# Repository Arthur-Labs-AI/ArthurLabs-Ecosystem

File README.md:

# ArthurLabs Ecosystem

Monorepo for the ArthurLabs products: **Nexus**, an AI engineering harness; **Sentry**, a local-first AI QA desktop app; **A.R.T.H.U.R.**, a local-first knowledge app; and the **ArthurLabs website**.

| Project | Path | What it is | Stack |
| --- | --- | --- | --- |
| **Nexus** | [`systems/nexus`](systems/nexus) | AI engineering assistant. A deterministic controller owns routing, attempts, verification and completion; the model implements. Ships in two editions: **Nexus DSH** and **Nexus Native** (see below). | Rust, Tauri v2, React, TypeScript, PowerShell/POSIX installers |
| **Sentry** | [`systems/sentry`](systems/sentry) | Local-first AI QA. OpenCode, DeepSeek and GLM (via Claude Code) independently investigate one immutable project snapshot and return findings, evidence, token usage and persistent run history. | TypeScript, pnpm + Turbo monorepo, Electron desktop, CLI |
| **A.R.T.H.U.R.** | [`systems/arthur`](systems/arthur) | Local-first knowledge app. Captures text and Android voice, distills it into knowledge objects with source provenance, projects, relations and immutable revision history, with recall and review-first evolution. One native runtime owns an app-local SQLite store. | Tauri v2, React, TypeScript, Rust, Android |
| **Website** | [`website`](website) | Marketing site for the ArthurLabs product line (Suite, Studio, Nexus, Sentry, Hardware). | Next.js, React, Tailwind, GSAP, Playwright |

Studio and Hardware appear as pages on the website only. Their implementations are not in this repository. Import history: [Nexus](docs/integration/NEXUS-IMPORT-REPORT.md), [Sentry](docs/integration/SENTRY-IMPORT-REPORT.md), [A.R.T.H.U.R.](docs/integration/ARTHUR-IMPORT-REPORT.md).

## Repository layout

```
.
├── systems/
│   ├── nexus/
│   │   ├── native/             Nexus Native: Rust workspace (kernel, broker, daemon, CLI, tools, store, runtime)
│   │   ├── apps/nexus-desktop  Nexus Native desktop app (Tauri, React + Rust) and release packaging
│   │   ├── runtime/, ui/       Nexus DSH: pinned DSH runtime, vendored agent, patches, Control Room UI
│   │   ├── bin/, config/, scripts/  `aih` commands, profiles, registry config, helpers (DSH)
│   │   ├── docs/               Architecture, operations, Linux guide
│   │   └── setup.sh, setup.ps1 Installers (Linux, Windows) for Nexus DSH
│   ├── sentry/
│   │   ├── apps/               desktop, cli, runtime
│   │   ├── packages/           run-engine, snapshot-engine, harnesses (claude-code, deepseek, opencode), persistence, ...
│   │   └── docs/               Setup, security, architecture, ADRs
│   └── arthur/
│       ├── apps/arthur         Tauri app (React UI + Rust runtime + SQLite store), Android
│       ├── packages/, src/     Shared packages and the older CLI/HTTP TypeScript runtime (frozen)
│       └── docs/, hardware/    Architecture, milestone gates, hardware notes
├── website/                    Next.js site (self-contained)
├── docs/integration/           Import and validation reports
└── .github/workflows/          CI: Nexus release workflow
```

## Nexus

Nexus moves engineering state out of the model and into deterministic controller records. Task identity, attempts, verification evidence, review requirements and completion live in the controller, and the UI observes that state. Key points:

- Execution classes (`deterministic`, `engineer_normal`, `engineer_deep`, `reviewer`, `solver`) bound to models by an engineering profile.
- Independent, read-only review when policy requires it.
- Durable task state and fail-closed behavior on missing or corrupt records.

Details: [`systems/nexus/README.md`](systems/nexus/README.md) and [`systems/nexus/docs`](systems/nexus/docs).

### Two editions

Both editions are maintained. Neither replaces the other.

| | **Nexus DSH** | **Nexus Native** |
| --- | --- | --- |
| Built on | The DeepSeek Harness (DSH) runtime: its sessions, tools, permissions, Git integration and web UI | A Rust engine with its own kernel, broker, daemon and sandboxed tools |
| Interface | Universal Nexus app and Control Room, opened with `aih -Open` | Tauri desktop app |
| Install | `setup.sh` (Linux) or `setup.ps1` (Windows) | `.deb` / `.dmg` from [Releases](https://github.com/Arthur-Labs-AI/ArthurLabs-Ecosystem/releases), or build from source |
| Platforms | Windows and Linux x86_64 | Linux x86_64 and macOS Apple Silicon |
| Code | `runtime/`, `ui/`, `bin/`, `config/`, `scripts/` | `native/`, `apps/nexus-desktop/` |

### Platform support

| Platform | Nexus DSH | Nexus Native |
| --- | --- | --- |
| Linux x86_64 | Supported | Full app: engine, sandbox, `.deb` package (Debian/Ubuntu, glibc 2.39+) |
| Linux ARM64 | Not documented | Development builds (Fedora 44 verified). Release packaging does not target ARM64. |
| macOS (Apple Silicon) | Not documented | Full app. The sandboxed Linux engine runs in an embedded headless microVM (Apple Virtualization.framework, no UTM or SSH), about 3 s to ready. Builds without the engine image are a UI-only shell. See [`M4-EMBEDDED-ENGINE-REPORT.md`](systems/nexus/M4-EMBEDDED-ENGINE-REPORT.md). |
| Windows | Supported | Not part of the native release workflow |

### Run Nexus DSH from source

Linux (user-scoped install, no sudo):

```sh
cd systems/nexus
./setup.sh
aih-key        # set your provider key
aih -Open      # open the app
```

Windows: run `setup.ps1` from PowerShell. See [`systems/nexus/README.md`](systems/nexus/README.md) and the [Linux guide](systems/nexus/docs/linux.md).

### Run Nexus Native from source

Needs Rust and Node.js 22+. On Fedora, first install `gtk3-devel webkit2gtk4.1-devel librsvg2-devel patchelf`.

```sh
cd systems/nexus/apps/nexus-desktop
npm ci
npm run desktop
```

See [`apps/nexus-desktop/README.md`](systems/nexus/apps/nexus-desktop/README.md) for environment variables and troubleshooting.

### Checks

```sh
# Nexus Native frontend
cd systems/nexus/apps/nexus-desktop
npm run typecheck && npm run lint && npm test

# Nexus Native Rust workspace
cd systems/nexus/native
cargo fmt --check && cargo clippy --all-targets && cargo test

# Nexus DSH
cd systems/nexus
aih-test
```

## Sentry

Sentry imports a project into a managed copy with an immutable revision, then lets one to three agents investigate it independently. Projects and history stay local. Selected agents send relevant source and evidence to the providers you configure, so review their policies before importing confidential code.

- **Platform:** Windows 11 x64 with WSL2 (Ubuntu preferred). Native Linux desktop is deferred.
- **Latest stable:** [Sentry v1.0.2](https://github.com/Mert1026/Sentry/releases/tag/v1.0.2). The ZIP is unsigned and bootstraps its Linux runtime online. There is no automatic updater.
- **Install and use:** `sentry setup`, `sentry open`, `sentry doctor`, and `sentry cli ... --json` for automation. See [`systems/sentry/README.md`](systems/sentry/README.md).

Develop (Node 22+, pnpm 9.12.3):

```sh
cd systems/sentry
pnpm install --frozen-lockfile
pnpm build
pnpm test
pnpm --filter @qa/desktop dev:electron
```

Development needs a Linux or WSL environment with systemd user services, bubblewrap and socat. See [`CONTRIBUTING.md`](systems/sentry/CONTRIBUTING.md) and the [documentation index](systems/sentry/docs/README.md).

## A.R.T.H.U.R.

A.R.T.H.U.R. keeps your knowledge in an app-local SQLite store owned by one native runtime; the UI reaches it through `ArthurClient` and native commands. Model responses only *propose* candidates. Native code validates authority, source spans and expected revisions before anything is committed. Cloud features need provider credentials and can send relevant content to the selected provider.

- **Status:** in development. M05 synchronization is a dormant qualification candidate, not an enabled feature. Production stays on schema v9 with closed trust/LAN activation. See [M05 readiness](systems/arthur/docs/architecture/m05-activation-readiness.md).
- **Legacy runtime:** the older CLI/HTTP TypeScript runtime under `src/` is under a [frozen subsystem policy](systems/arthur/docs/competition/FROZEN_SUBSYSTEMS.md) and is not the app's authoritative store.

Develop (Node.js 24.13.1 and Rust 1.99.1 in CI):

```sh
cd systems/arthur
npm ci
npm run arthur:install
npm run arthur:dev                # browser preview with a native-free client (no SQLite)
cd apps/arthur && npm run tauri -- dev   # the real native app
```

Android builds need the JDK, Android SDK/NDK and the Rust Android target. See [`systems/arthur/README.md`](systems/arthur/README.md) and [`apps/arthur/README.md`](systems/arthur/apps/arthur/README.md).

Checks (from `systems/arthur`): `npm run test:architecture` and `npm run arthur:check`, plus `cargo fmt`, `cargo clippy` and `cargo test` against `apps/arthur/src-tauri/Cargo.toml` as listed in its README.

## Website

```sh
cd website
npm ci
npm run dev        # http://localhost:3000
npm run build
npm run typecheck
```

Needs Node.js 20.9+. End-to-end tests run with Playwright against the production export. See [`website/README.md`](website/README.md) for the full procedure, routes and structure.

## Releases

**Nexus Native** installers are built by [`.github/workflows/nexus-release.yml`](.github/workflows/nexus-release.yml):

- Trigger: push a `nexus-v*` tag, or run **Nexus release** from the Actions tab with a tag name.
- Linux job: builds and content-verifies the `.deb`.
- Engine image job: builds the Fedora ARM64 guest image and kernel on an ARM64 Linux runner.
- macOS job: builds the app with the embedded VM engine and packages the arm64 `.dmg` (about 430 MB). It is ad-hoc signed and not notarized, so Gatekeeper will warn on first launch (right-click, then Open).
- The workflow creates a **draft** GitHub release with both installers and SHA-256 files. It never publishes on its own.

Published builds are listed under [Releases](https://github.com/Arthur-Labs-AI/ArthurLabs-Ecosystem/releases). Sentry releases are published separately on its own repository (link above).

## Contributing

- Commits follow Conventional Commits with a scope: `feat(native): …`, `fix(registry): …`, `docs: …`, `test(native): …`.
- Branches are named `type/short-slug`, for example `feat/nexus-release-workflow`.
- Work in the subproject you are changing and run its checks before opening a PR.
- A.R.T.H.U.R. enforces architecture boundaries in CI (`npm run test:architecture`); run it before opening a PR.
- Sentry has its own rules (branching, review, agent instruction files): read [`systems/sentry/CONTRIBUTING.md`](systems/sentry/CONTRIBUTING.md) first.

## Security

Never commit provider keys, `auth.json`, `.env` files, logs, or session captures. If a credential is committed, rotate it right away. See [`systems/nexus/SECURITY.md`](systems/nexus/SECURITY.md) and the Sentry [threat model](systems/sentry/docs/security/V1_THREAT_MODEL.md).

## License

Licenses are per project:

- **Sentry:** MIT, see [`systems/sentry/LICENSE`](systems/sentry/LICENSE).
- **A.R.T.H.U.R.:** `UNLICENSED` in its `package.json` (proprietary, no open-source license).
- **Nexus and website:** no license file yet. Until one is added, all rights are reserved by the authors.

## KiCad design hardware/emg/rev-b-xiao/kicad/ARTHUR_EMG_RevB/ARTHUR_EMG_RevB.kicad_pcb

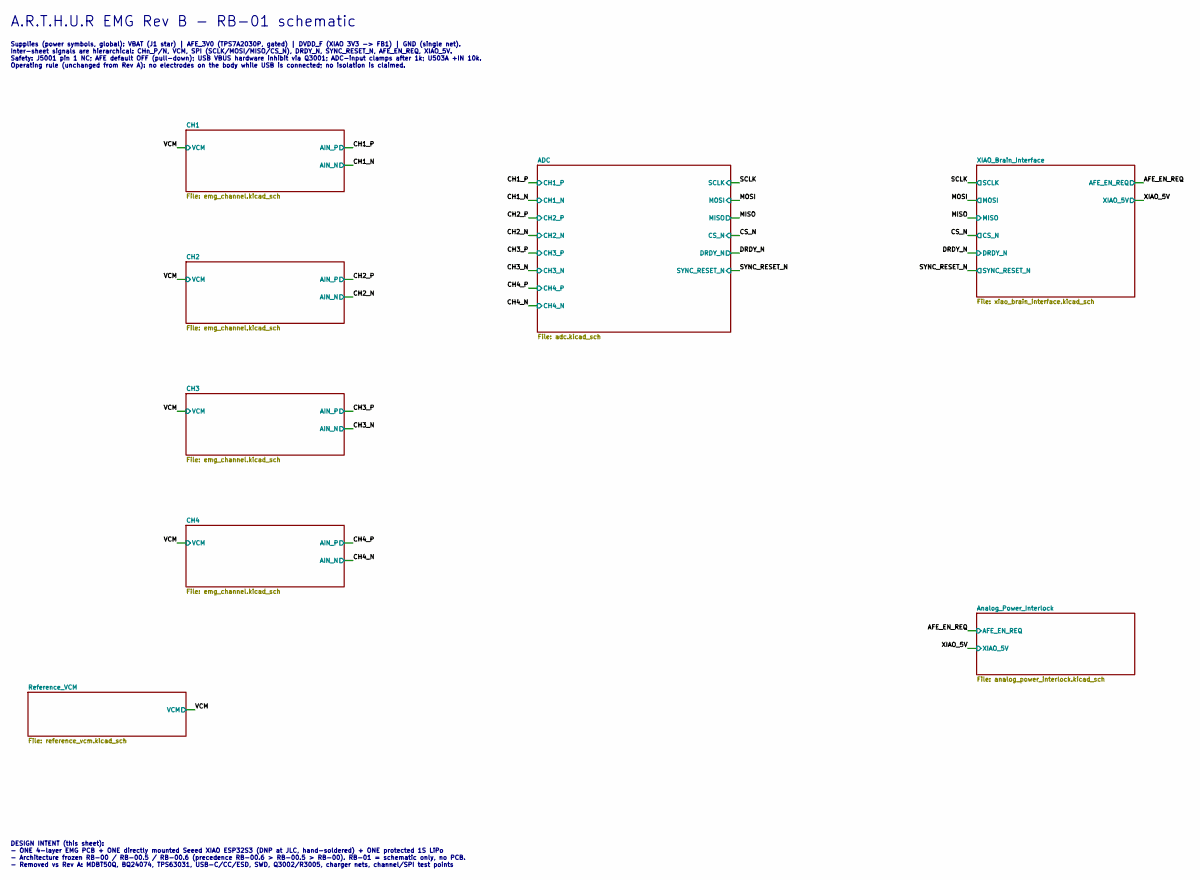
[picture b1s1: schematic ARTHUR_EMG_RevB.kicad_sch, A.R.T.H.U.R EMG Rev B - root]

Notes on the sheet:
DESIGN INTENT (this sheet): - ONE 4-layer EMG PCB + ONE directly mounted Seeed XIAO ESP32S3 (DNP at JLC, hand-soldered) + ONE protected 1S LiPo - Architecture frozen RB-00 / RB-00.5 / RB-00.6 (precedence RB-00.6 > RB-00.5 > RB-00). RB-01 = schematic only, no PCB. - Removed vs Rev A: MDBT50Q, BQ2407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
A.R.T.H.U.R EMG Rev B - RB-01 schematic
Supplies (power symbols, global): VBAT (J1 star) | AFE_3V0 (TPS7A2030P, gated) | DVDD_F (XIAO 3V3 -> FB1) | GND (single net). Inter-sheet signals are hierarchical: CHn_P/N, VCM, SPI (SCLK/MOSI/MISO/CS_N), DRDY_N, SYNC_RESET_N, AFE_EN_REQ, XIAO_5V. Safety: J5001 pin 1 NC; AFE default OFF (pull-down)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

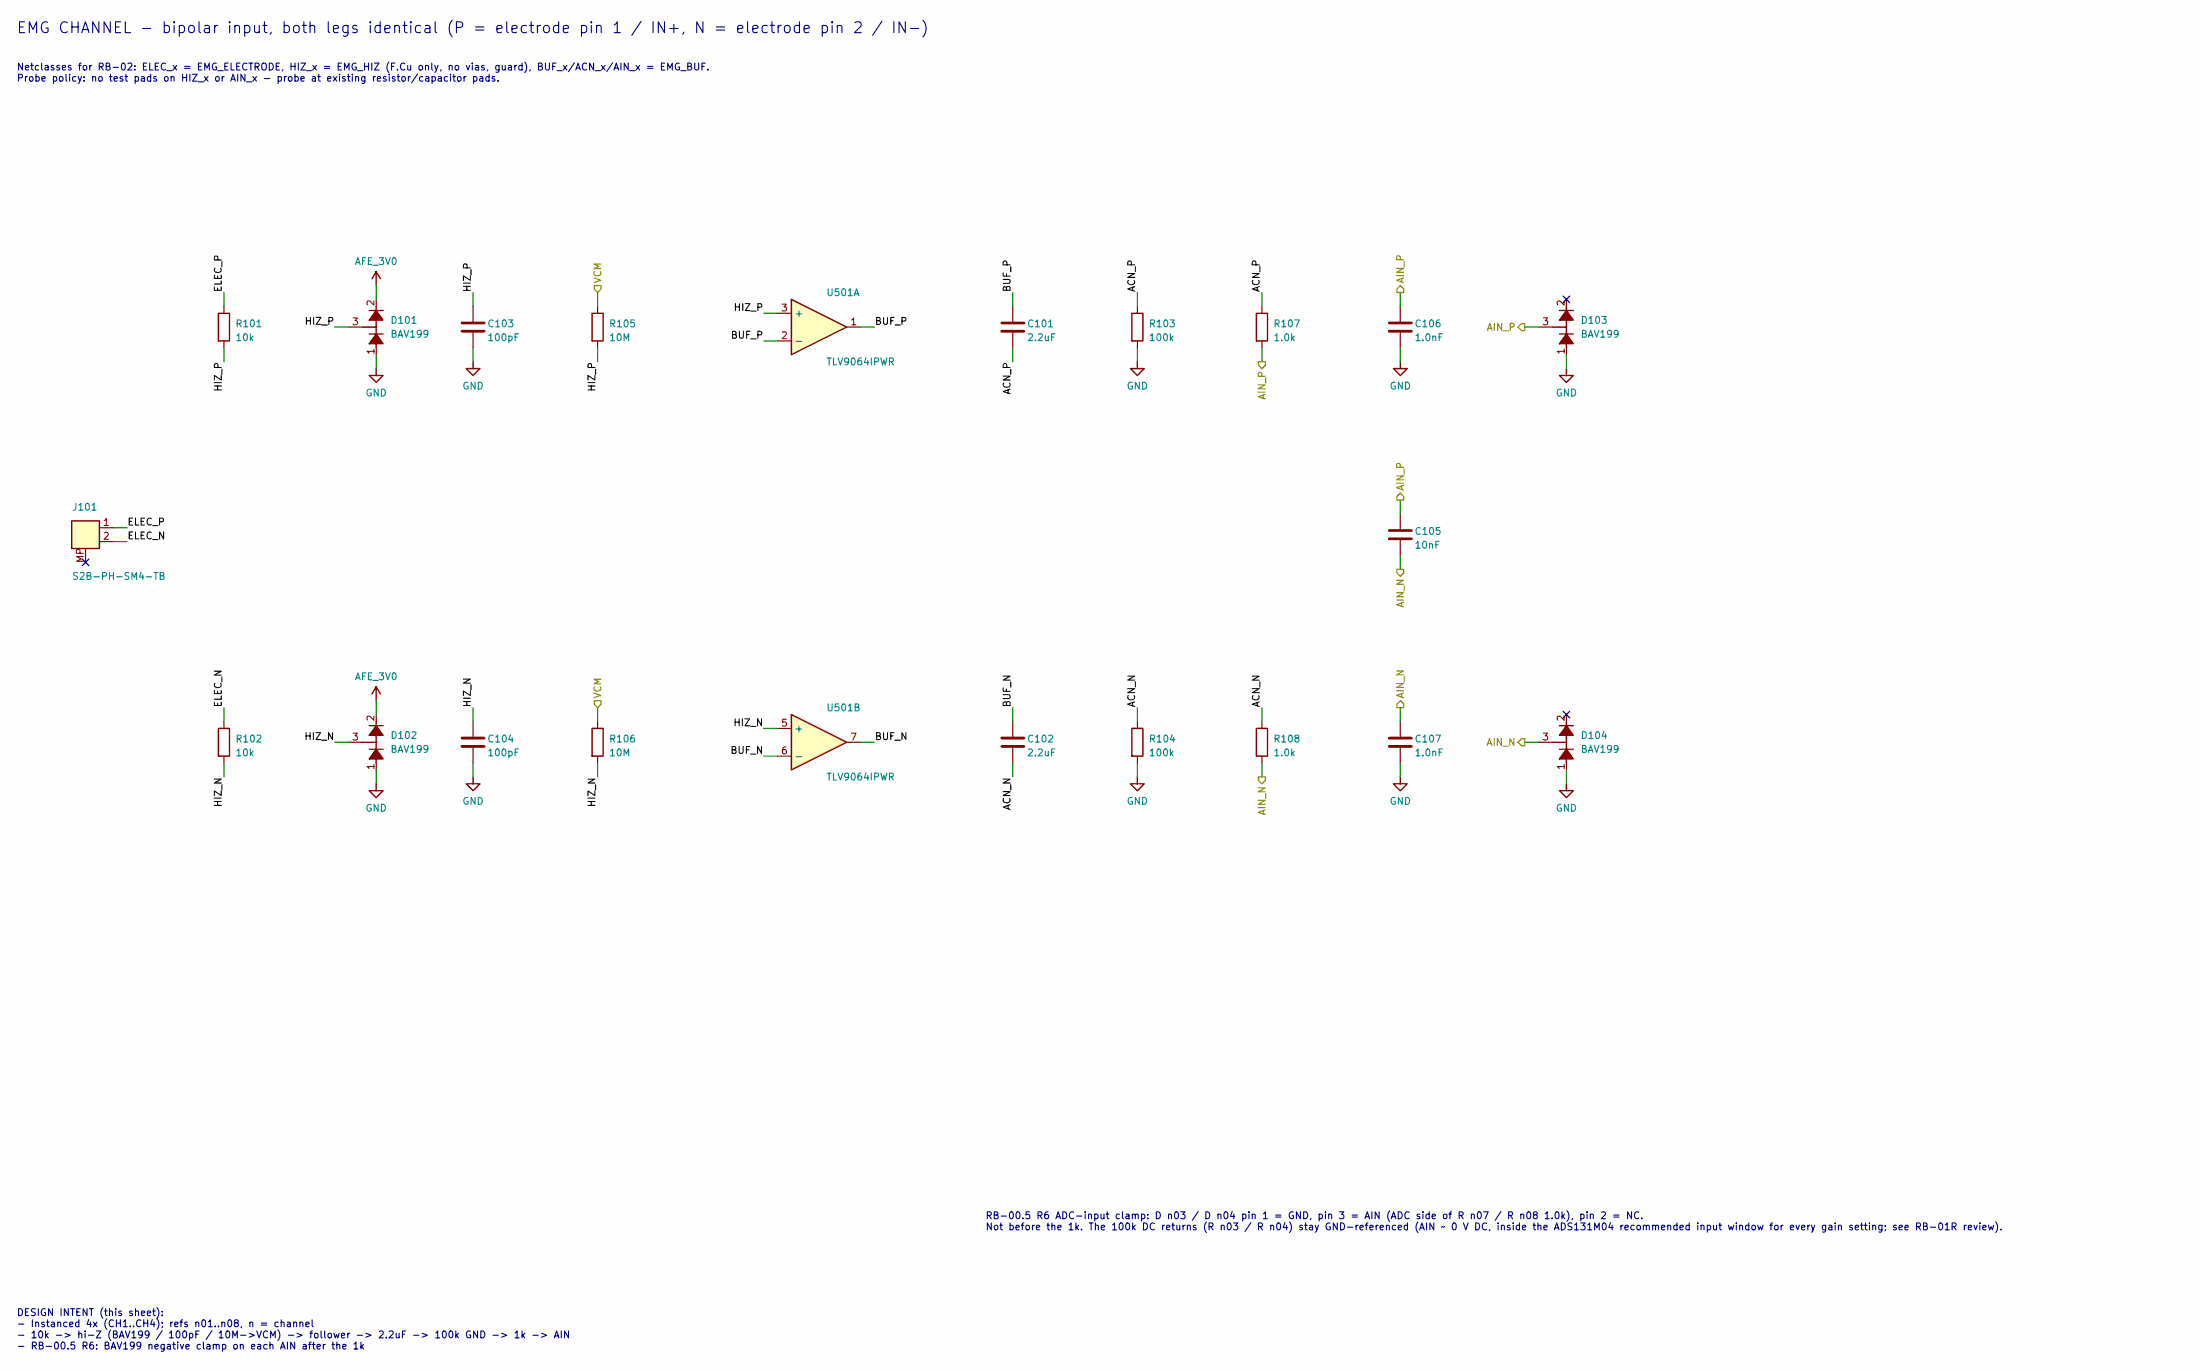
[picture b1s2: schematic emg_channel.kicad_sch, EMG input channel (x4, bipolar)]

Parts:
C101, C102: 2.2uF; C_0603_1608Metric; MPN 0603B225K160NT; LCSC C43922
C103, C104: 100pF; C_0603_1608Metric; MPN CL10C101JB8NNNC; LCSC C14858
C105: 10nF; C_0603_1608Metric; MPN C1608C0G1H103JT000N; LCSC C76599
C106, C107: 1.0nF; C_0603_1608Metric; MPN 0603CG102J500NT; LCSC C1636
D101, D102, D103, D104: BAV199; SOT-23; MPN BAV199,215; LCSC C40919
J101: S2B-PH-SM4-TB; JST_PH_S2B-PH-SM4-TB_1x02-1MP_P2.00mm_Horizontal; MPN S2B-PH-SM4-TB(LF)(SN); LCSC C295747
R101, R102: 10k; R_0603_1608Metric; MPN RC0603FR-0710KL; LCSC C98220
R103, R104: 100k; R_0603_1608Metric; MPN 0603WAF1003T5E; LCSC C25803
R105, R106: 10M; R_0603_1608Metric; MPN RC0603FR-0710ML; LCSC C114606
R107, R108: 1.0k; R_0603_1608Metric; MPN 0603WAF1001T5E; LCSC C21190
U501: TLV9064IPWR; TSSOP-14_4.4x5mm_P0.65mm; MPN TLV9064IPWR; LCSC C779410

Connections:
/CH1/ACN_N: C102.2, R104.1, R108.1
/CH1/ACN_P: C101.2, R103.1, R107.1
/CH1/BUF_N: C102.1, U501.6 (-), U501.7
/CH1/BUF_P: C101.1, U501.1, U501.2 (-)
/CH1/ELEC_N: J101.2, R102.1
/CH1/ELEC_P: J101.1, R101.1
/CH1/HIZ_N: C104.1, D102.3 (K1/A2), R102.2, R106.2, U501.5 (+)
/CH1/HIZ_P: C103.1, D101.3 (K1/A2), R101.2, R105.2, U501.3 (+)
/CH1_N: C105.2, C107.1, D104.3 (K1/A2), R108.2; also elsewhere on the board
/CH1_P: C105.1, C106.1, D103.3 (K1/A2), R107.2; also elsewhere on the board
/CH2/BUF_N: U501.13 (-), U501.14; also elsewhere on the board
/CH2/BUF_P: U501.8, U501.9 (-); also elsewhere on the board
/CH2/HIZ_N: U501.12 (+); also elsewhere on the board
/CH2/HIZ_P: U501.10 (+); also elsewhere on the board
/VCM: R105.1, R106.1; also elsewhere on the board
AFE_3V0: D101.2 (K2), D102.2 (K2); also elsewhere on the board
GND: C103.2, C104.2, C106.2, C107.2, D101.1 (A1), D102.1 (A1), D103.1 (A1), D104.1 (A1), R103.2, R104.2; also elsewhere on the board

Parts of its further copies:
C201, C202, C301, C302, C401, C402: 2.2uF; C_0603_1608Metric; MPN 0603B225K160NT; LCSC C43922
C203, C204, C303, C304, C403, C404: 100pF; C_0603_1608Metric; MPN CL10C101JB8NNNC; LCSC C14858
C205, C305, C405: 10nF; C_0603_1608Metric; MPN C1608C0G1H103JT000N; LCSC C76599
C206, C207, C306, C307, C406, C407: 1.0nF; C_0603_1608Metric; MPN 0603CG102J500NT; LCSC C1636
D201, D202, D203, D204, D301, D302, D303, D304, D401, D402, D403, D404: BAV199; SOT-23; MPN BAV199,215; LCSC C40919
J201, J301, J401: S2B-PH-SM4-TB; JST_PH_S2B-PH-SM4-TB_1x02-1MP_P2.00mm_Horizontal; MPN S2B-PH-SM4-TB(LF)(SN); LCSC C295747
R201, R202, R301, R302, R401, R402: 10k; R_0603_1608Metric; MPN RC0603FR-0710KL; LCSC C98220
R203, R204, R303, R304, R403, R404: 100k; R_0603_1608Metric; MPN 0603WAF1003T5E; LCSC C25803
R205, R206, R305, R306, R405, R406: 10M; R_0603_1608Metric; MPN RC0603FR-0710ML; LCSC C114606
R207, R208, R307, R308, R407, R408: 1.0k; R_0603_1608Metric; MPN 0603WAF1001T5E; LCSC C21190

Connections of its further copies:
/CH2/ACN_N: C202.2, R204.1, R208.1
/CH2/ACN_P: C201.2, R203.1, R207.1
/CH2/BUF_N: C202.1; also elsewhere on the board
/CH2/BUF_P: C201.1; also elsewhere on the board
/CH2/ELEC_N: J201.2, R202.1
/CH2/ELEC_P: J201.1, R201.1
/CH2/HIZ_N: C204.1, D202.3 (K1/A2), R202.2, R206.2; also elsewhere on the board
/CH2/HIZ_P: C203.1, D201.3 (K1/A2), R201.2, R205.2; also elsewhere on the board
/CH2_N: C205.2, C207.1, D204.3 (K1/A2), R208.2; also elsewhere on the board
/CH2_P: C205.1, C206.1, D203.3 (K1/A2), R207.2; also elsewhere on the board
/CH3/ACN_N: C302.2, R304.1, R308.1
/CH3/ACN_P: C301.2, R303.1, R307.1
/CH3/BUF_N: C302.1; also elsewhere on the board
/CH3/BUF_P: C301.1; also elsewhere on the board
/CH3/ELEC_N: J301.2, R302.1
/CH3/ELEC_P: J301.1, R301.1
/CH3/HIZ_N: C304.1, D302.3 (K1/A2), R302.2, R306.2; also elsewhere on the board
/CH3/HIZ_P: C303.1, D301.3 (K1/A2), R301.2, R305.2; also elsewhere on the board
/CH3_N: C305.2, C307.1, D304.3 (K1/A2), R308.2; also elsewhere on the board
/CH3_P: C305.1, C306.1, D303.3 (K1/A2), R307.2; also elsewhere on the board
/CH4/ACN_N: C402.2, R404.1, R408.1
/CH4/ACN_P: C401.2, R403.1, R407.1
/CH4/BUF_N: C402.1; also elsewhere on the board
/CH4/BUF_P: C401.1; also elsewhere on the board
/CH4/ELEC_N: J401.2, R402.1
/CH4/ELEC_P: J401.1, R401.1
/CH4/HIZ_N: C404.1, D402.3 (K1/A2), R402.2, R406.2; also elsewhere on the board
/CH4/HIZ_P: C403.1, D401.3 (K1/A2), R401.2, R405.2; also elsewhere on the board
/CH4_N: C405.2, C407.1, D404.3 (K1/A2), R408.2; also elsewhere on the board
/CH4_P: C405.1, C406.1, D403.3 (K1/A2), R407.2; also elsewhere on the board
/VCM: R205.1, R206.1, R305.1, R306.1, R405.1, R406.1; also elsewhere on the board
AFE_3V0: D201.2 (K2), D202.2 (K2), D301.2 (K2), D302.2 (K2), D401.2 (K2), D402.2 (K2); also elsewhere on the board
GND: C203.2, C204.2, C206.2, C207.2, C303.2, C304.2, C306.2, C307.2, C403.2, C404.2, C406.2, C407.2, D201.1 (A1), D202.1 (A1), D203.1 (A1), D204.1 (A1), D301.1 (A1), D302.1 (A1), D303.1 (A1), D304.1 (A1), D401.1 (A1), D402.1 (A1), D403.1 (A1), D404.1 (A1), R203.2, R204.2, R303.2, R304.2, R403.2, R404.2; also elsewhere on the board

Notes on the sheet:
EMG CHANNEL - bipolar input, both legs identical (P = electrode pin 1 / IN+, N = electrode pin 2 / IN-)
Netclasses for RB-02: ELEC_x = EMG_ELECTRODE, HIZ_x = EMG_HIZ (F.Cu only, no vias, guard), BUF_x/ACN_x/AIN_x = EMG_BUF. Probe policy: no test pads on HIZ_x or AIN_x - probe at existing resistor/capacitor pads.
RB-00.5 R6 ADC-input clamp: D n03 / D n04 pin 1 = GND, pin 3 = AIN (ADC side of R n07 / R n08 1.0k), pin 2 = NC. Not before the 1k. The 100k DC returns (R n03 / R n04) stay GND-referenced (AIN ~ 0 V DC, inside the ADS131M04 recommended input window for every gain setting; see RB-01R review).
DESIGN INTENT (this sheet): - Instanced 4x (CH1..CH4); refs n01..n08, n = channel - 10k -> hi-Z (BAV199 / 100pF / 10M->VCM) -> follower -> 2.2uF -> 100k GND -> 1k -> AIN - RB-00.5 R6: BAV199 negative clamp on each AIN after the 1k

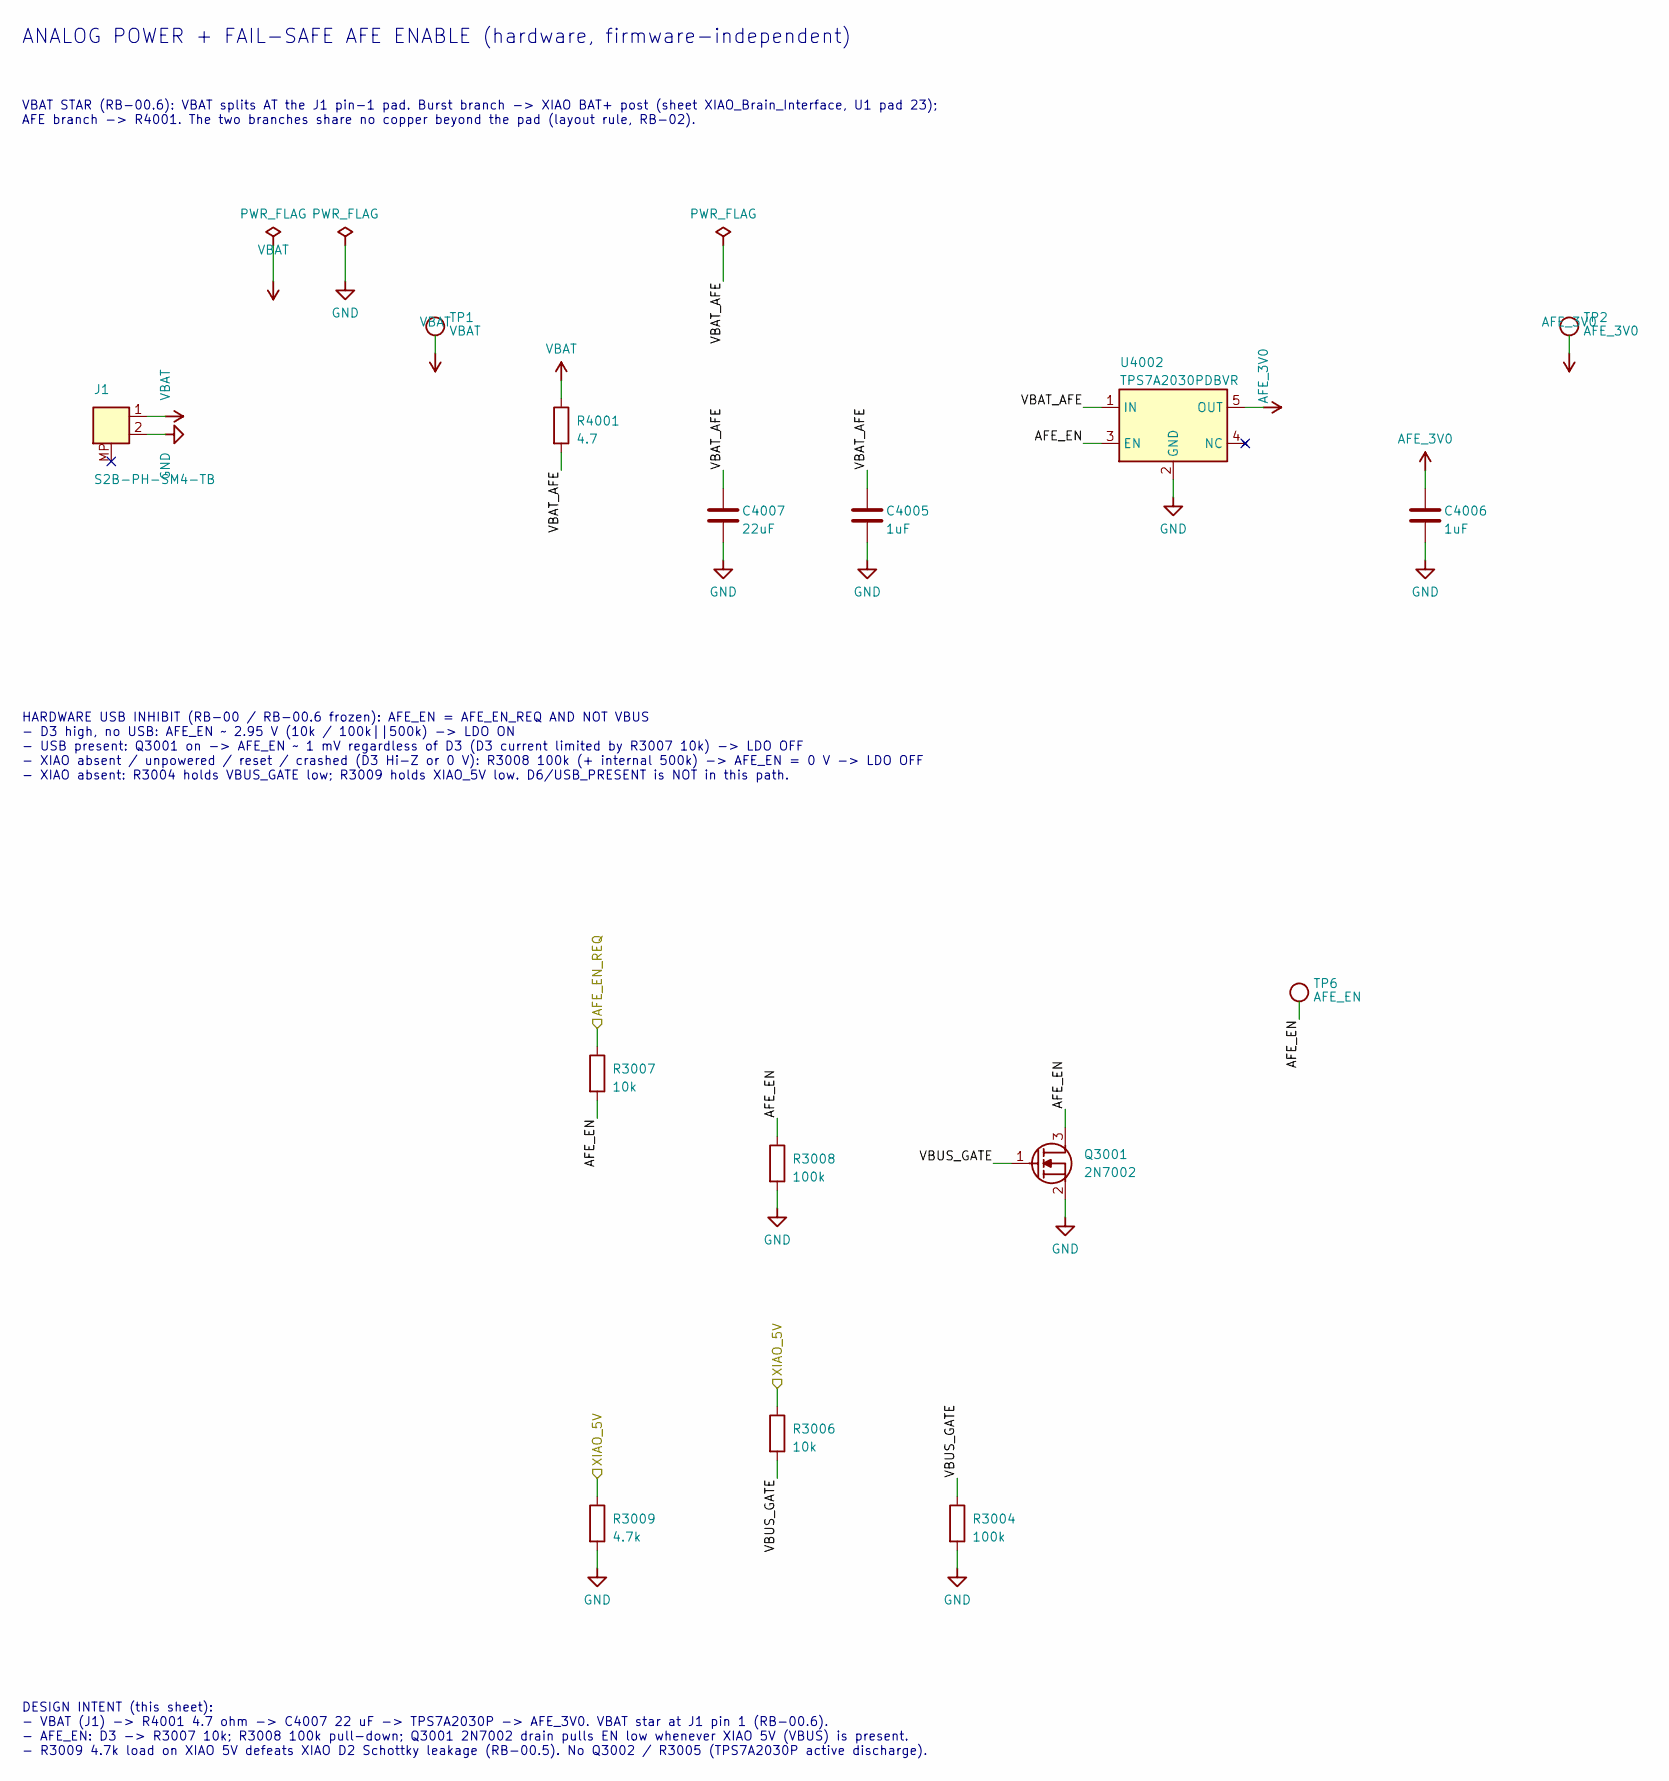
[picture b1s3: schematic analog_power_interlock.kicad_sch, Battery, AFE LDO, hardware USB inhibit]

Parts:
C4005, C4006: 1uF; C_0603_1608Metric; MPN GENERIC (spec-defined; JLC Basic part s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; JLC_Class Basic (expected)
C4007: 22uF; C_0805_2012Metric; MPN GENERIC (spec-defined; JLC Basic part s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; JLC_Class Basic (expected)
J1: S2B-PH-SM4-TB; JST_PH_S2B-PH-SM4-TB_1x02-1MP_P2.00mm_Horizontal; MPN S2B-PH-SM4-TB(LF)(SN) (provisional - 'e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; JLC_Class Extended (expected)
Q3001: 2N7002; SOT-23; MPN 2N7002; JLC_Class Basic (expected)
R3004, R3008: 100k; R_0603_1608Metric; MPN GENERIC (spec-defined; JLC Basic part s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; JLC_Class Basic (expected)
R3006, R3007: 10k; R_0603_1608Metric; MPN GENERIC (spec-defined; JLC Basic part s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; JLC_Class Basic (expected)
R3009: 4.7k; R_0603_1608Metric; MPN GENERIC (spec-defined; JLC Basic part s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; JLC_Class Basic (expected)
R4001: 4.7; R_0603_1608Metric; MPN GENERIC (spec-defined; JLC Basic part s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; JLC_Class Basic (expected)
TP1: VBAT; TestPoint_Pad_D1.5mm; MPN N/A (bare copper pad); JLC_Class N/A (not assembled)
TP2: AFE_3V0; TestPoint_Pad_D1.5mm; MPN N/A (bare copper pad); JLC_Class N/A (not assembled)
TP6: AFE_EN; TestPoint_Pad_D1.5mm; MPN N/A (bare copper pad); JLC_Class N/A (not assembled)
U4002: TPS7A2030PDBVR; SOT-23-5; MPN TPS7A2030PDBVR; JLC_Class Extended (expected)

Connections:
/AFE_EN_REQ: R3007.1; also elsewhere on the board
/Analog_Power_Interlock/AFE_EN: Q3001.3 (D), R3007.2, R3008.1, TP6.1, U4002.3 (EN)
/Analog_Power_Interlock/VBAT_AFE: C4005.1, C4007.1, R4001.2, U4002.1 (IN)
/Analog_Power_Interlock/VBUS_GATE: Q3001.1 (G), R3004.1, R3006.2
/XIAO_5V: R3006.1, R3009.1; also elsewhere on the board
AFE_3V0: C4006.1, TP2.1, U4002.5 (OUT); also elsewhere on the board
GND: C4005.2, C4006.2, C4007.2, J1.2, Q3001.2 (S), R3004.2, R3008.2, R3009.2, U4002.2 (GND); also elsewhere on the board
VBAT: J1.1, R4001.1, TP1.1; also elsewhere on the board

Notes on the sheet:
ANALOG POWER + FAIL-SAFE AFE ENABLE (hardware, firmware-independent)
VBAT STAR (RB-00.6): VBAT splits AT the J1 pin-1 pad. Burst branch -> XIAO BAT+ post (sheet XIAO_Brain_Interface, U1 pad 23); AFE branch -> R4001. The two branches share no copper beyond the pad (layout rule, RB-02).
DESIGN INTENT (this sheet): - VBAT (J1) -> R4001 4.7 ohm -> C4007 22 uF -> TPS7A2030P -> AFE_3V0. VBAT star at J1 pin 1 (RB-00.6). - AFE_EN: D3 -> R3007 10k; R3008 100k pull-down; Q3001 2N7002 drain pulls EN low whenever XIAO 5V (VBUS) is present. - R3009 4.7k load on XIAO 5V defeats XIAO D2 Schott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
HARDWARE USB INHIBIT (RB-00 / RB-00.6 frozen): AFE_EN = AFE_EN_REQ AND NOT VBUS - D3 high, no USB: AFE_EN ~ 2.95 V (10k / 100k||500k) -> LDO ON - USB present: Q3001 on -> AFE_EN ~ 1 mV regardless of D3 (D3 current limited by R3007 10k) -> LDO OFF - XIAO absent / unpowered / reset / crashed (D3 Hi-Z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

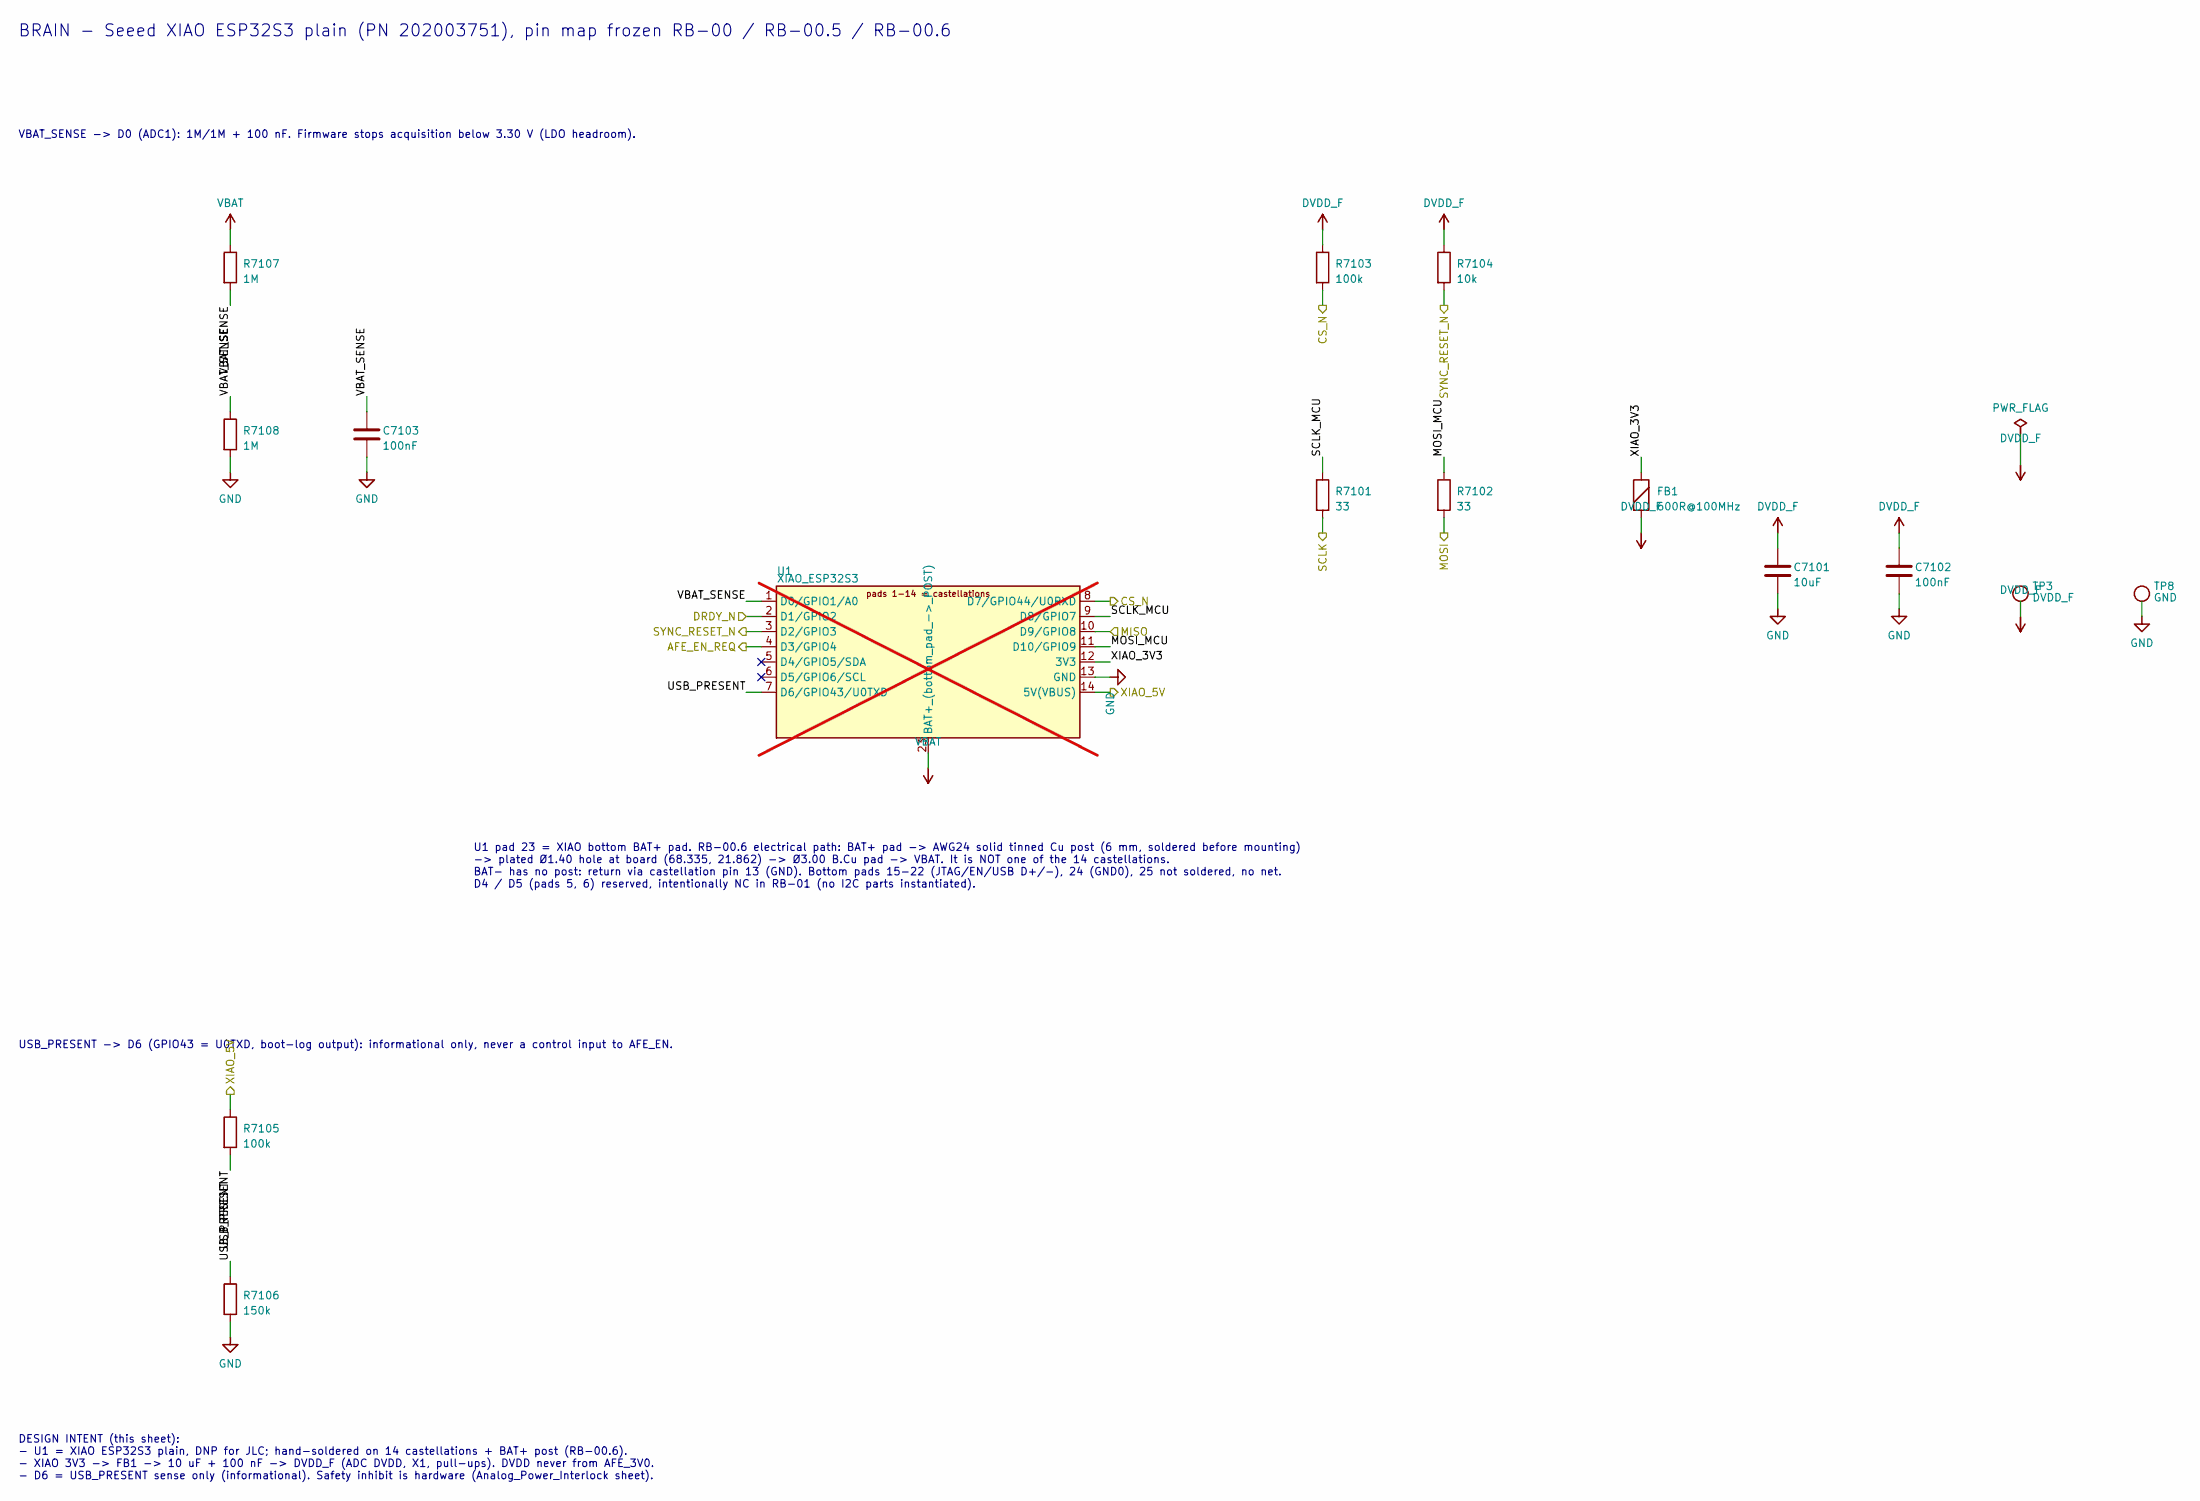
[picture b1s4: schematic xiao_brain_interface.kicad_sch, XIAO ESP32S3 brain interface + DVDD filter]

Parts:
C7101: 10uF; C_0603_1608Metric; MPN GENERIC (spec-defined; JLC Basic part s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; JLC_Class Basic (expected)
C7102, C7103: 100nF; C_0603_1608Metric; MPN GENERIC (spec-defined; JLC Basic part s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; JLC_Class Basic (expected)
FB1: 600R@100MHz; L_0603_1608Metric; MPN GENERIC (spec-defined; JLC Basic part s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; JLC_Class Basic (expected)
R7101, R7102: 33; R_0603_1608Metric; MPN GENERIC (spec-defined; JLC Basic part s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; JLC_Class Basic (expected)
R7103, R7105: 100k; R_0603_1608Metric; MPN GENERIC (spec-defined; JLC Basic part s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; JLC_Class Basic (expected)
R7104: 10k; R_0603_1608Metric; MPN GENERIC (spec-defined; JLC Basic part s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; JLC_Class Basic (expected)
R7106: 150k; R_0603_1608Metric; MPN GENERIC (spec-defined; JLC Basic part s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; JLC_Class Basic (expected)
R7107, R7108: 1M; R_0603_1608Metric; MPN GENERIC (spec-defined; JLC Basic part s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; JLC_Class Basic (expected)
TP3: DVDD_F; TestPoint_Pad_D1.5mm; MPN N/A (bare copper pad); JLC_Class N/A (not assembled)
TP8: GND; TestPoint_Pad_D1.5mm; MPN N/A (bare copper pad); JLC_Class N/A (not assembled)
U1: XIAO_ESP32S3; XIAO_ESP32S3_HANDSOLDER; MPN Seeed PN 202003751 (XIAO ESP32S3 plain,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; JLC_Class N/A - DNP at JLC (bought retail, hand-s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; not fitted

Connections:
/AFE_EN_REQ: U1.4 (D3/GPIO4); also elsewhere on the board
/CS_N: R7103.2, U1.8 (D7/GPIO44/U0RXD); also elsewhere on the board
/DRDY_N: U1.2 (D1/GPIO2); also elsewhere on the board
/MISO: U1.10 (D9/GPIO8); also elsewhere on the board
/MOSI: R7102.2; also elsewhere on the board
/SCLK: R7101.2; also elsewhere on the board
/SYNC_RESET_N: R7104.2, U1.3 (D2/GPIO3); also elsewhere on the board
/XIAO_5V: R7105.1, U1.14 (5V(VBUS)); also elsewhere on the board
/XIAO_Brain_Interface/MOSI_MCU: R7102.1, U1.11 (D10/GPIO9)
/XIAO_Brain_Interface/SCLK_MCU: R7101.1, U1.9 (D8/GPIO7)
/XIAO_Brain_Interface/USB_PRESENT: R7105.2, R7106.1, U1.7 (D6/GPIO43/U0TXD)
/XIAO_Brain_Interface/VBAT_SENSE: C7103.1, R7107.2, R7108.1, U1.1 (D0/GPIO1/A0)
/XIAO_Brain_Interface/XIAO_3V3: FB1.1, U1.12 (3V3)
DVDD_F: C7101.1, C7102.1, FB1.2, R7103.1, R7104.1, TP3.1; also elsewhere on the board
GND: C7101.2, C7102.2, C7103.2, R7106.2, R7108.2, TP8.1, U1.13 (GND); also elsewhere on the board
VBAT: R7107.1, U1.23 (BAT+_(bottom_pad_->_POST)); also elsewhere on the board

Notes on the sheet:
U1 pad 23 = XIAO bottom BAT+ pad. RB-00.6 electrical path: BAT+ pad -> AWG24 solid tinned Cu post (6 mm, soldered before mounting) -> plated Ø1.40 hole at board (68.335, 21.862) -> Ø3.00 B.Cu pad -> VBAT. It is NOT one of the 14 castellations. BAT- has no post: return via castellation pin 13 (GND).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
VBAT_SENSE -> D0 (ADC1): 1M/1M + 100 nF. Firmware stops acquisition below 3.30 V (LDO headroom).
USB_PRESENT -> D6 (GPIO43 = U0TXD, boot-log output): informational only, never a control input to AFE_EN.
DESIGN INTENT (this sheet): - U1 = XIAO ESP32S3 plain, DNP for JLC; hand-soldered on 14 castellations + BAT+ post (RB-00.6). - XIAO 3V3 -> FB1 -> 10 uF + 100 nF -> DVDD_F (ADC DVDD, X1, pull-ups). DVDD never from AFE_3V0. - D6 = USB_PRESENT sense only (informational). Safety inhibit is hardware (An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
BRAIN - Seeed XIAO ESP32S3 plain (PN 202003751), pin map frozen RB-00 / RB-00.5 / RB-00.6
